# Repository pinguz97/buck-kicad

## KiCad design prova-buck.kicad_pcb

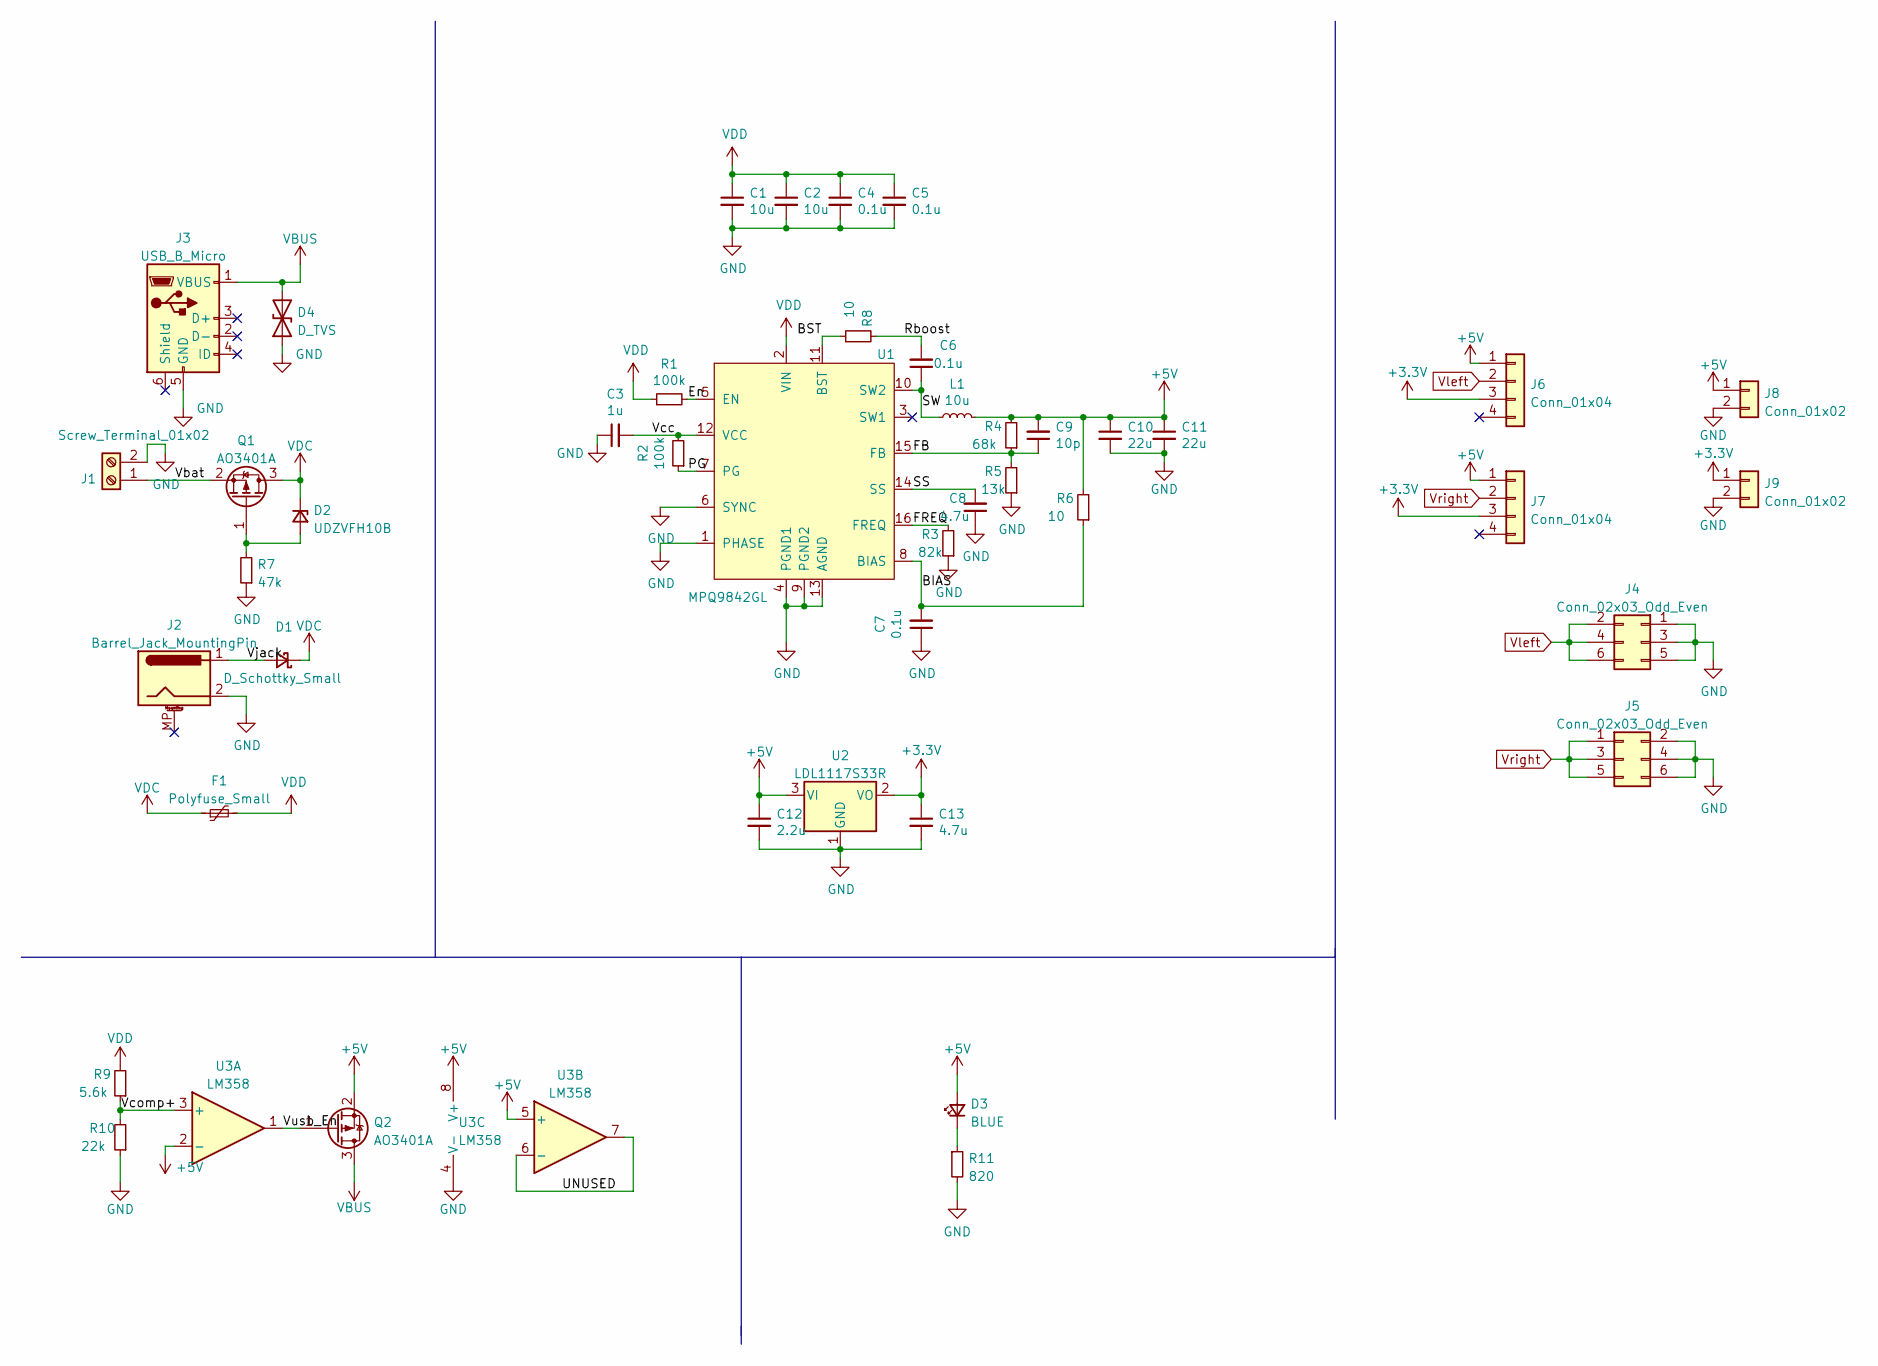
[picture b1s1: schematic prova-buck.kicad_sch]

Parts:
C1, C2: 10u; C_1206_3216Metric; LCSC Part # C13585
C3: 1u; C_0603_1608Metric; LCSC Part # C15849
C4, C5, C7: 0.1u; C_0603_1608Metric; LCSC Part # C14663
C6: 0.1u; C_0402_1005Metric; LCSC Part # C307331
C8: 4.7u; C_0603_1608Metric; LCSC Part # C19666
C9: 10p; C_0603_1608Metric; LCSC Part # C1634
C10, C11: 22u; C_1206_3216Metric; LCSC Part # C12891
C12: 2.2u; C_0603_1608Metric; LCSC Part # C23630
C13: 4.7u; C_0805_2012Metric; LCSC Part # C1779
D1: D_Schottky_Small; D_SMA; LCSC Part # C8678
D2: UDZVFH10B; D_SOD-323_HandSoldering
D3: BLUE; LED_0603_1608Metric; LCSC Part # C72041
D4: D_TVS; D_SOD-323_HandSoldering
F1: Polyfuse_Small; Fuse_2016_HandSolder
J1: Screw_Terminal_01x02; TerminalBlock_Phoenix_PT-1,5-2-3.5-H_1x02_P3.50mm_Horizontal
J2: Barrel_Jack_MountingPin; BarrelJack_Horizontal
J3: USB_B_Micro; USB_Micro-B_Amphenol_10118194_Horizontal
J4, J5: Conn_02x03_Odd_Even; PinHeader_2x03_P2.54mm_Vertical
J6, J7: Conn_01x04; PinHeader_1x04_P2.54mm_Vertical
J8, J9: Conn_01x02; Solder_wire_PAD
L1: 10u; L_Sunlord_MWSA0518_5.4x5.2mm; LCSC Part # C408412
Q1, Q2: AO3401A; SOT-23; LCSC Part # C15127
R1, R2: 100k; R_0603_1608Metric; LCSC Part # C25803
R3: 82k; R_0603_1608Metric; LCSC Part # C23254
R4: 68k; R_0603_1608Metric; LCSC Part # C23231
R5: 13k; R_0603_1608Metric; LCSC Part # C22797
R6: 10; R_0603_1608Metric; LCSC Part # C22859
R7: 47k; R_0603_1608Metric; LCSC Part # C25819
R8: 10; R_0402_1005Metric; LCSC Part # C25077
R9: 5.6k; R_0603_1608Metric; LCSC Part # C23189
R10: 22k; R_0603_1608Metric; LCSC Part # C31850
R11: 820; R_0603_1608Metric; LCSC Part # C23253
U1: MPQ9842GL; QFN16_3mm_x_4mm
U2: LDL1117S33R; SOT-223-3_TabPin2
U3: LM358; SOIC-8_3.9x4.9mm_P1.27mm; LCSC Part # C7950

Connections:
+3V3: C13.1, J6.3, J7.3, J9.1, U2.2 (VO)
+5V: C9.2, C10.1, C11.1, C12.1, D3.2 (A), J6.1, J7.1, J8.1, L1.2, Q2.2 (S), R4.2, R6.2, U2.3 (VI), U3.2 (-), U3.5 (+), U3.8 (V+)
/BIAS: C7.2, R6.1, U1.8 (BIAS)
/BST: R8.1, U1.11 (BST)
/En: R1.2, U1.5 (EN)
/FB: C9.1, R4.1, R5.2, U1.15 (FB)
/FREQ: R3.2, U1.16 (FREQ)
/PG: R2.1, U1.7 (PG)
/Rboost: C6.2, R8.2
/SS: C8.2, U1.14 (SS)
/SW: C6.1, L1.1, U1.10 (SW2)
/UNUSED: U3.6 (-), U3.7
/Vbat: J1.1, Q1.2 (S)
/Vcc: C3.2, R2.2, U1.12 (VCC)
/Vcomp+: R9.1, R10.2, U3.3 (+)
/Vjack: D1.2 (A), J2.1
/Vusb_En: Q2.1 (G), U3.1
GND: C1.2, C2.2, C3.1, C4.2, C5.2, C7.1, C8.1, C10.2, C11.2, C12.2, C13.2, D4.1 (A1), J1.2, J2.2, J3.5 (GND), J4.1, J4.3, J4.5, J5.2, J5.4, J5.6, J8.2, J9.2, R3.1, R5.1, R7.1, R10.1, R11.2, U1.1 (PHASE), U1.4 (PGND1), U1.6 (SYNC), U1.9 (PGND2), U1.13 (AGND), U2.1 (GND), U3.4 (V-)
unnamed: D2.2 (A), Q1.1 (G), R7.2
unnamed: D3.1 (K), R11.1
VBUS: D4.2 (A2), J3.1 (VBUS), Q2.3 (D)
VDC: D1.1 (K), D2.1 (K), F1.1, Q1.3 (D)
VDD: C1.1, C2.1, C4.1, C5.1, F1.2, R1.1, R9.2, U1.2 (VIN)
Vleft: J4.2, J4.4, J4.6, J6.2
Vright: J5.1, J5.3, J5.5, J7.2

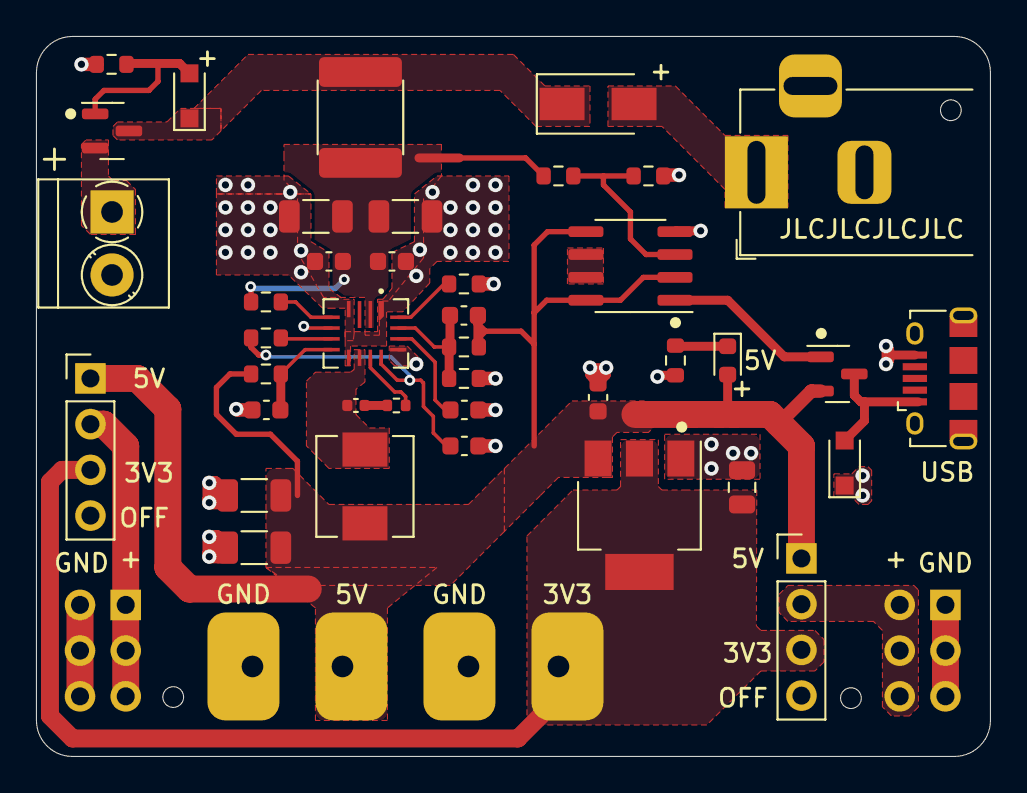
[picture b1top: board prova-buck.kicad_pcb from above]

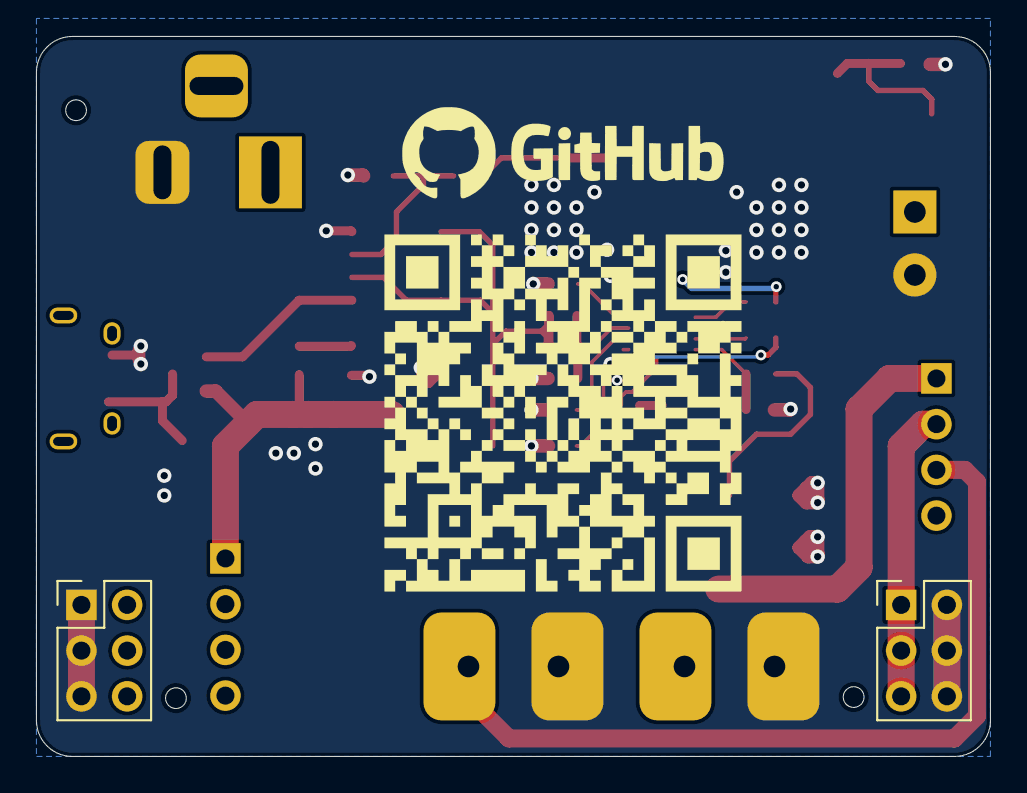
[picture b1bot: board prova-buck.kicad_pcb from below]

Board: 2 copper layers, 53.0 x 40.0 mm, 44 parts (2 on the bottom side), 25 nets.

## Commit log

2022-03-05 fist commit
2022-03-05 added MPQ9841GL datasheet
2022-03-06 Added footprints
2022-03-06 "second commit"
2022-03-06 "third commit"
2022-03-07 "Updated project"
2022-03-07 "Added Inductor, Buck 3d models"
2022-03-08 " Added power supply selector"
2022-03-09 "added LDO"
2022-03-14 "added JLCPB and Mouser components"
2022-03-16 Added .gitignore
2022-03-19 "Generated gerbers"
2022-03-19 Generated BOM adn CPL file
